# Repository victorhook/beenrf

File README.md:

# BeeNrf 

## How to get started with EFM8B Busy Bee Ubuntu 22.04

### 1. Install stable wine.
Install wine according to winehq: https://wiki.winehq.org/Ubuntu
Don't follow normal ubuntu guidelines, since it requires manually installing `wine32`
which wants to break half of my system.

### 2. Launch
cd $SIMPLICITY_INSTALLATION && WINEPATH=$SIMPLICITY_INSTALLATION ./studio

## BOM
| Geared 3V motor x2 | 32kr * 2 |
| Front wheel |  |
| nrf24l01 | 18kr | 
| Busy Bee 8-bit | 10kr |
| Mosfet | 2 |
| Battery charg | |

## PCB Layers
1. RF signals
2. Ground  <- Don't break!
3. Power   <- Don't break!
4. Other signals

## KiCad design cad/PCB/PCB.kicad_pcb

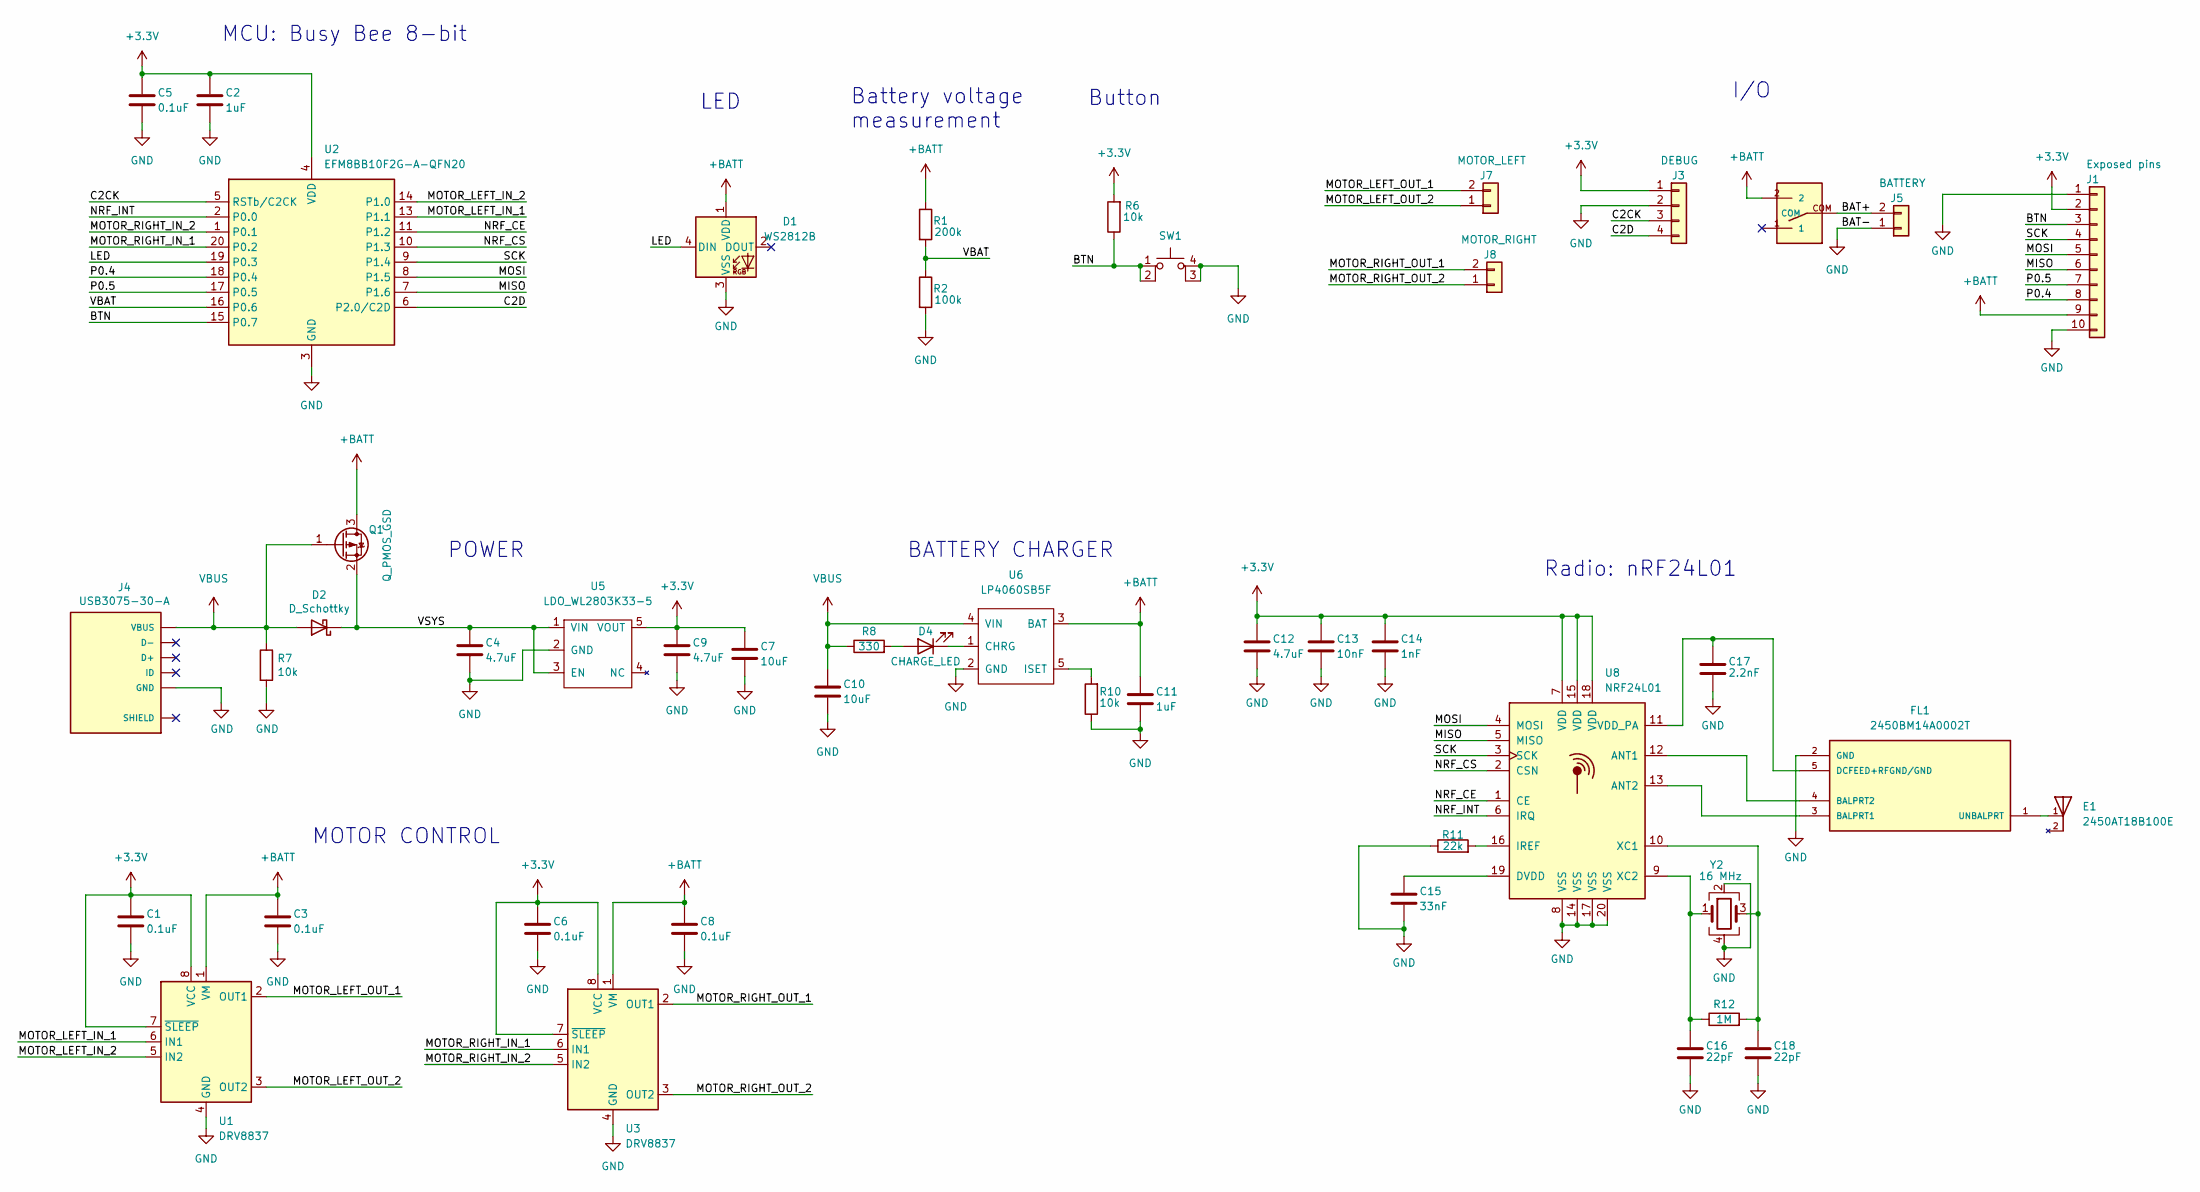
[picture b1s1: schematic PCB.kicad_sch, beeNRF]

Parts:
C1, C3, C5, C6, C8: 0.1uF; C_0402_1005Metric
C2, C11: 1uF; C_0402_1005Metric
C4, C9, C12: 4.7uF; C_0402_1005Metric
C7, C10: 10uF; C_0805_2012Metric
C13: 10nF; C_0402_1005Metric
C14: 1nF; C_0402_1005Metric
C15: 33nF; C_0402_1005Metric
C16, C18: 22pF; C_0402_1005Metric
C17: 2.2nF; C_0402_1005Metric
D1: WS2812B; LED_WS2812B_PLCC4_5.0x5.0mm_P3.2mm
D2: D_Schottky; D_SOD-123
D4: CHARGE_LED; LED_0603_1608Metric
E1: 2450AT18B100E; 2450AT18B100E_pcb_antenna; PARTREV 4.0
FL1: 2450BM14A0002T; 2450BM14A0002; PARTREV 6/13/2012
J1: Exposed pins; PinSocket_1x10_P2.54mm_Vertical
J3: DEBUG; JST_SH_SM04B-SRSS-TB_1x04-1MP_P1.00mm_Horizontal_No_silk
J4: USB3075-30-A; PARTREV D3
J5: BATTERY; Conn_01x02_VBAT
J7: MOTOR_LEFT; Conn_01x02_VBAT
J8: MOTOR_RIGHT; Conn_01x02_VBAT
Q1: Q_PMOS_GSD; SOT-23
R1: 200k; R_0402_1005Metric
R2: 100k; R_0402_1005Metric
R6, R7, R10: 10k; R_0402_1005Metric
R8: 330; R_0402_1005Metric
R11: 22k; R_0402_1005Metric
R12: 1M; R_0402_1005Metric
SW1: RESET; PTS815
U1, U3: DRV8837; WSON-8-1EP_2x2mm_P0.5mm_EP0.9x1.6mm
U2: EFM8BB10F2G-A-QFN20; SiliconLabs_QFN-20-1EP_3x3mm_P0.5mm_EP1.8x1.8mm
U5: LDO_WL2803K33-5; SOT-89-5
U6: LP4060SB5F; SOT-23-5
U7: SK12D07VG4; toggle_switch_SK12D07VG4
U8: NRF24L01; QFN-20-1EP_4x4mm_P0.5mm_EP2.5x2.5mm
Y2: 16 MHz; Crystal_SMD_2520-4Pin_2.5x2.0mm

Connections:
+3.3V: C1.1, C2.1, C5.1, C6.1, C7.1, C9.1, C12.1, C13.1, C14.1, J1.2, J3.1, R6.2, U1.7 (~SLEEP), U1.8 (VCC), U2.4 (VDD), U3.7 (~SLEEP), U3.8 (VCC), U5.5 (VOUT), U8.7 (VDD), U8.15 (VDD), U8.18 (VDD)
+BATT: C3.1, C8.1, C11.1, D1.1 (VDD), J1.9, Q1.3 (D), R1.1, U1.1 (VM), U3.1 (VM), U6.3 (BAT), U7.2
/BAT+: J5.2, U7.COM
/BTN: J1.3, R6.1, SW1.1, SW1.2, U2.15 (P0.7)
/C2CK: J3.3, U2.5 (RSTb/C2CK)
/C2D: J3.4, U2.6 (P2.0/C2D)
/LED: D1.4 (DIN), U2.19 (P0.3)
/MISO: J1.6, U2.7 (P1.6), U8.5 (MISO)
/MOSI: J1.5, U2.8 (P1.5), U8.4 (MOSI)
/MOTOR_LEFT_IN_1: U1.6 (IN1), U2.13 (P1.1)
/MOTOR_LEFT_IN_2: U1.5 (IN2), U2.14 (P1.0)
/MOTOR_LEFT_OUT_1: J7.2, U1.2 (OUT1)
/MOTOR_LEFT_OUT_2: J7.1, U1.3 (OUT2)
/MOTOR_RIGHT_IN_1: U2.20 (P0.2), U3.6 (IN1)
/MOTOR_RIGHT_IN_2: U2.1 (P0.1), U3.5 (IN2)
/MOTOR_RIGHT_OUT_1: J8.2, U3.2 (OUT1)
/MOTOR_RIGHT_OUT_2: J8.1, U3.3 (OUT2)
/NRF_CE: U2.11 (P1.2), U8.1 (CE)
/NRF_CS: U2.10 (P1.3), U8.2 (CSN)
/NRF_INT: U2.2 (P0.0), U8.6 (IRQ)
/P0.4: J1.8, U2.18 (P0.4)
/P0.5: J1.7, U2.17 (P0.5)
/SCK: J1.4, U2.9 (P1.4), U8.3 (SCK)
/VBAT: R1.2, R2.1, U2.16 (P0.6)
/VSYS: C4.1, D2.1 (K), Q1.2 (S), U5.1 (VIN), U5.3 (EN)
GND: C1.2, C2.2, C3.2, C4.2, C5.2, C6.2, C7.2, C8.2, C9.2, C10.2, C11.2, C12.2, C13.2, C14.2, C15.2, C16.2, C17.2, C18.2, D1.3 (VSS), FL1.2 (GND), J1.1, J1.10, J3.2, J4.5 (GND), J5.1, R2.2, R7.2, R10.1, R11.1, SW1.3 (K), SW1.4 (A), U1.4 (GND), U1.9 (GND), U2.3 (GND), U2.12 (GND), U2.21 (GND), U3.4 (GND), U3.9 (GND), U5.2 (GND), U6.2 (GND), U8.8 (VSS), U8.14 (VSS), U8.17 (VSS), U8.20 (VSS), Y2.2, Y2.4
unnamed: C15.1, U8.19 (DVDD)
unnamed: C16.1, R12.1, U8.9 (XC2), Y2.1
unnamed: C17.1, FL1.5 (DCFEED+RFGND/GND), U8.11 (VDD_PA)
unnamed: C18.1, R12.2, U8.10 (XC1), Y2.3
unnamed: D4.1 (K), U6.1 (CHRG)
unnamed: D4.2 (A), R8.2
unnamed: E1.1, FL1.1 (UNBALPRT)
unnamed: FL1.3 (BALPRT1), U8.13 (ANT2)
unnamed: FL1.4 (BALPRT2), U8.12 (ANT1)
unnamed: R10.2, U6.5 (ISET)
unnamed: R11.2, U8.16 (IREF)
VBUS: C10.1, D2.2 (A), J4.1 (VBUS), Q1.1 (G), R7.1, R8.1, U6.4 (VIN)

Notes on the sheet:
Battery voltage measurement
BATTERY CHARGER
I/O
MCU: Busy Bee 8-bit
Radio: nRF24L01
MOTOR CONTROL
LED
POWER
Button

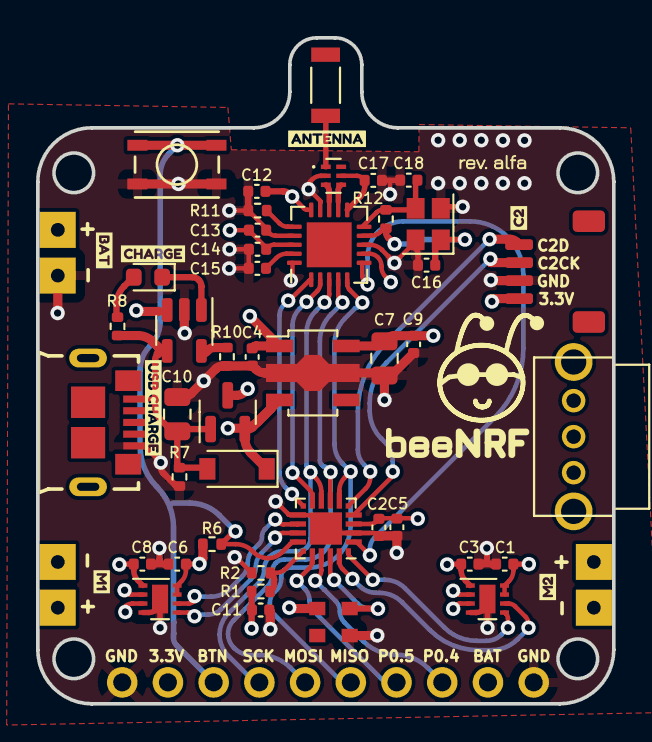
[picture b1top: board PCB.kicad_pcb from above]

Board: 4 copper layers, 32.0 x 37.0 mm, 54 parts (0 on the bottom side), 38 nets.

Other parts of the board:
kibuzzard-63246B6F: G***; kibuzzard-63246B6F
kibuzzard-63246BBB: G***; kibuzzard-63246BBB
kibuzzard-63246BF5: G***; kibuzzard-63246BF5
kibuzzard-63246C29: G***; kibuzzard-63246C29
kibuzzard-63247AD7: G***; kibuzzard-63247AD7
kibuzzard-63247AF7: G***; kibuzzard-63247AF7
kibuzzard-63247D50: G***; kibuzzard-63247D50

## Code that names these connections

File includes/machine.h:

#ifndef MACHINE_H
#define MACHINE_H

#include "core.h"


#define PIN_NRF_INT       P0_B0
#define PIN_MOTOR_RIGHT_2 P0_B1  // M2
#define PIN_MOTOR_RIGHT_1 P0_B2  // M2
#define PIN_VBAT          P0_B6
#define PIN_BTN           P0_B7
#define PIN_MOTOR_LEFT_2  P1_B0
#define PIN_MOTOR_LEFT_1  P1_B1


//#define DEV_BOARD

#ifdef DEV_BOARD
    // Local devboard
    #define PIN_LED           P1_B4

    // SPI
    #define PIN_NRF_CE P1_B5
    #define PIN_NRF_CS P1_B6
    #define PIN_SCK    P1_B7
    #define PIN_MOSI   P1_B3
    #define PIN_MISO   P1_B2
#else
    // Real BeeNRF
    #define PIN_LED           P0_B3

    // SPI
    #define PIN_NRF_CE        P1_B2
    #define PIN_NRF_CS        P1_B3
    #define PIN_SCK           P1_B4
    #define PIN_MOSI          P1_B5
    #define PIN_MISO          P1_B6
#endif


#endif /* MACHINE_H */

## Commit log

2022-10-18 Just saving cad files
2022-10-28 Moved project to different directory. Most basic functionality of the robot is working. There's some fine-tuning to do!

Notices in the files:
parts and their libraries:
Copyright 2016 Accelerated Designs. All rights reserved.
